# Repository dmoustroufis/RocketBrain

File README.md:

# RocketBrain
A flight computer for model rockets in a HAT format for the Raspberry Pi Pico

Hardware characteristics  : 
* Primary 9 axis IMU 
* Secondary 6 axis IMU 
* Barometer 
* 128kB flash chip for vibration-safe data logging  
* micro sd card slot for data logging 
* LoRa tranceiver with 10km range 
* Output for 2 servos for Thrust Vector Control 
* Output for a Reaction Wheel motor (external driver is needed for the motor)
* 2 pyro channels 

The brain of the device is the Raspberry Pi Pico,
an ultra affordable, dual core, 32-bit microcontroller running at 125MHz.

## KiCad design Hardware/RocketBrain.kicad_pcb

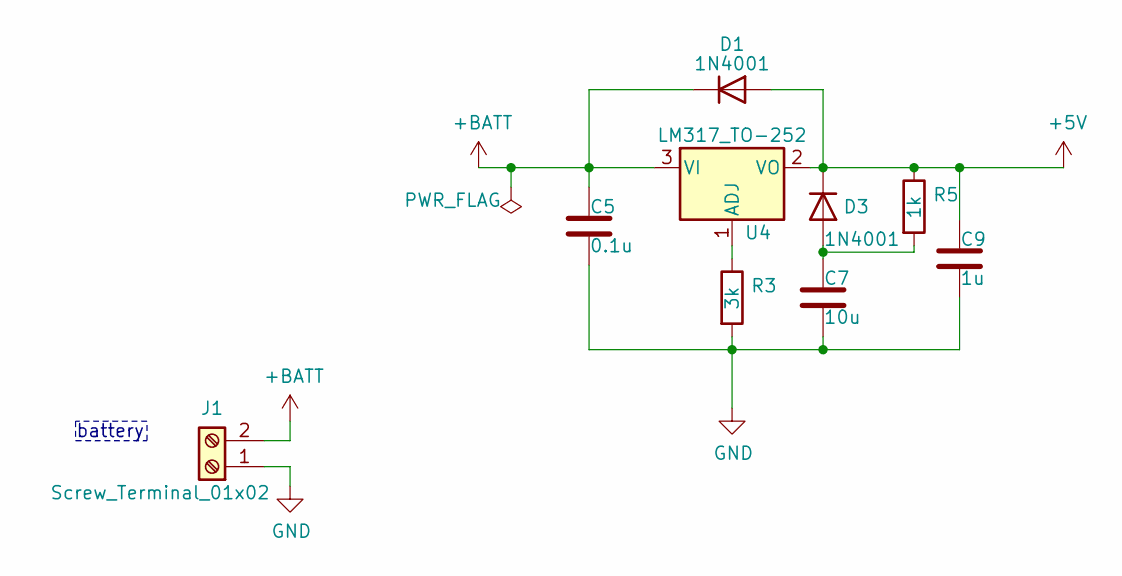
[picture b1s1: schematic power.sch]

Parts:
C5: 0.1u; C_0603_1608Metric
C7: 10u; C_0603_1608Metric
C9: 1u; C_0603_1608Metric
D1, D3: 1N4001; D_SOD-123F; Manufacturer_Part_Number 1N4001W
J1: Screw_Terminal_01x02; TerminalBlock_TE_282834-2_1x02_P2.54mm_Horizontal
R3: 3k; R_0603_1608Metric
R5: 1k; R_0603_1608Metric
U4: LM317_TO-252; TO-252-2; Manufacturer_Part_Number LM317AG-TN3-R

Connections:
+5V: C9.1, D1.2 (A), D3.1 (K), R5.1, U4.2 (VO); also elsewhere on the board
+BATT: C5.1, D1.1 (K), J1.2, U4.3 (VI); also elsewhere on the board
GND: C5.2, C7.2, C9.2, J1.1, R3.2; also elsewhere on the board
unnamed: C7.1, D3.2 (A), R5.2
unnamed: R3.1, U4.1 (ADJ)

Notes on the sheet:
battery

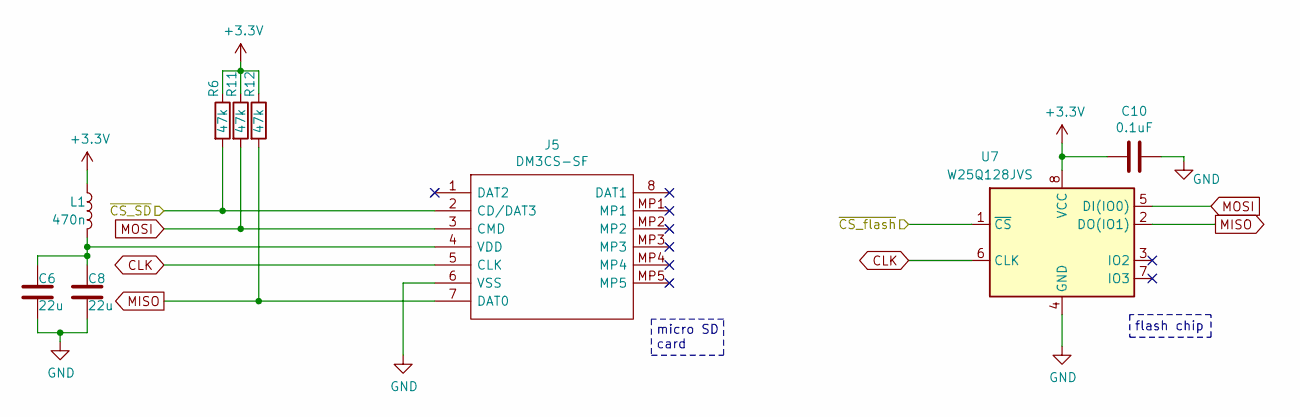
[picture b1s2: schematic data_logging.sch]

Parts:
C6, C8: 22u; C_0603_1608Metric
C10: 0.1uF; C_0603_1608Metric
J5: DM3CS-SF; DM3CSSF; Manufacturer_Part_Number DM3CS-SF; Mouser Part Number 798-DM3CSSF
L1: 470n; L_0603_1608Metric
R6, R11, R12: 47k; R_0603_1608Metric
U7: W25Q128JVS; SOIC-8_5.23x5.23mm_P1.27mm; Manufacturer_Part_Number W25Q128JVSIQ

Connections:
+3V3: C10.2, L1.1, R6.1, R11.1, R12.1, U7.8 (VCC); also elsewhere on the board
/Data Logging/~CS_SD: J5.2 (CD/DAT3), R6.2; also elsewhere on the board
/Data Logging/~CS_flash: U7.1 (~CS); also elsewhere on the board
CLK: J5.5 (CLK), U7.6 (CLK); also elsewhere on the board
GND: C6.2, C8.2, C10.1, J5.6 (VSS), U7.4 (GND); also elsewhere on the board
MISO: J5.7 (DAT0), R12.2, U7.2 (DO(IO1)); also elsewhere on the board
MOSI: J5.3 (CMD), R11.2, U7.5 (DI(IO0)); also elsewhere on the board
unnamed: C6.1, C8.1, J5.4 (VDD), L1.2

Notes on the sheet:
flash chip
micro SD card

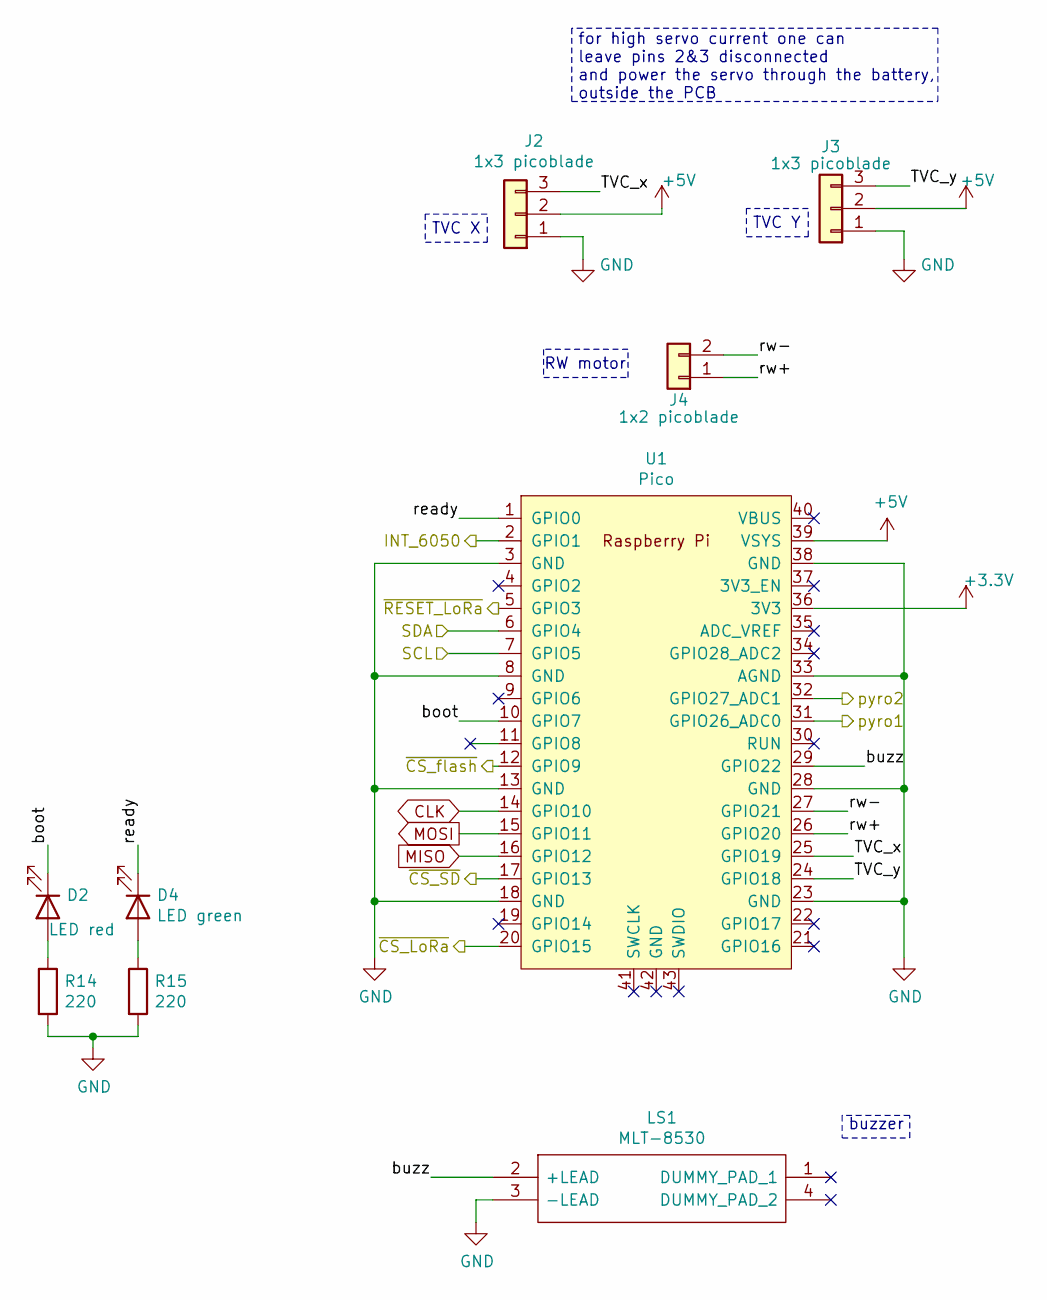
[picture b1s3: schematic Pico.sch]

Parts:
D2: LED red; LED_0603_1608Metric
D4: LED green; LED_0603_1608Metric
J2, J3: 1x3 picoblade; Molex_PicoBlade_53398-0371_1x03-1MP_P1.25mm_Vertical
J4: 1x2 picoblade; Molex_PicoBlade_53398-0271_1x02-1MP_P1.25mm_Vertical
LS1: MLT-8530; MLT8530; Manufacturer_Part_Number MLT-8530
R14, R15: 220; R_0603_1608Metric
U1: Pico; RPi_Pico_HAT_smd_mod

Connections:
+3V3: U1.36 (3V3); also elsewhere on the board
+5V: J2.2, J3.2, U1.39 (VSYS); also elsewhere on the board
/Data Logging/~CS_SD: U1.17 (GPIO13); also elsewhere on the board
/Data Logging/~CS_flash: U1.12 (GPIO9); also elsewhere on the board
/Pyro/pyro1: U1.31 (GPIO26_ADC0); also elsewhere on the board
/Pyro/pyro2: U1.32 (GPIO27_ADC1); also elsewhere on the board
/RPi Pico & Motors/INT_6050: U1.2 (GPIO1); also elsewhere on the board
/RPi Pico & Motors/SCL: U1.7 (GPIO5); also elsewhere on the board
/RPi Pico & Motors/SDA: U1.6 (GPIO4); also elsewhere on the board
/RPi Pico & Motors/TVC_x: J2.3, U1.25 (GPIO19)
/RPi Pico & Motors/TVC_y: J3.3, U1.24 (GPIO18)
/RPi Pico & Motors/boot: D2.1 (K), U1.10 (GPIO7)
/RPi Pico & Motors/buzz: LS1.2 (+LEAD), U1.29 (GPIO22)
/RPi Pico & Motors/ready: D4.1 (K), U1.1 (GPIO0)
/RPi Pico & Motors/rw+: J4.1, U1.26 (GPIO20)
/RPi Pico & Motors/rw-: J4.2, U1.27 (GPIO21)
/RPi Pico & Motors/~CS_LoRa: U1.20 (GPIO15); also elsewhere on the board
/RPi Pico & Motors/~RESET_LoRa: U1.5 (GPIO3); also elsewhere on the board
CLK: U1.14 (GPIO10); also elsewhere on the board
GND: J2.1, J3.1, LS1.3 (-LEAD), R14.2, R15.2, U1.3 (GND), U1.8 (GND), U1.13 (GND), U1.18 (GND), U1.23 (GND), U1.28 (GND), U1.33 (AGND), U1.38 (GND); also elsewhere on the board
MISO: U1.16 (GPIO12); also elsewhere on the board
MOSI: U1.15 (GPIO11); also elsewhere on the board
unnamed: D2.2 (A), R14.1
unnamed: D4.2 (A), R15.1

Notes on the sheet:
RW motor
TVC X
TVC Y
buzzer
for high servo current one can leave pins 2&3 disconnected and power the servo through the battery, outside the PCB

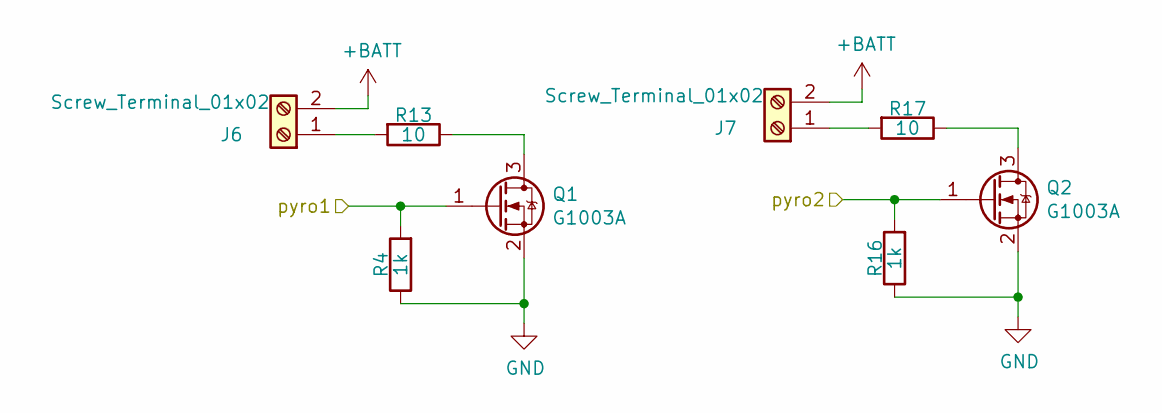
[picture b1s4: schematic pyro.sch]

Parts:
J6, J7: Screw_Terminal_01x02; TerminalBlock_TE_282834-2_1x02_P2.54mm_Horizontal
Q1, Q2: G1003A; SOT-23; Manufacturer_Part_Number G1003A
R4, R16: 1k; R_0603_1608Metric
R13, R17: 10; R_0603_1608Metric

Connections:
+BATT: J6.2, J7.2; also elsewhere on the board
/Pyro/pyro1: Q1.1 (G), R4.2; also elsewhere on the board
/Pyro/pyro2: Q2.1 (G), R16.2; also elsewhere on the board
GND: Q1.2 (S), Q2.2 (S), R4.1, R16.1; also elsewhere on the board
unnamed: J6.1, R13.2
unnamed: J7.1, R17.2
unnamed: Q1.3 (D), R13.1
unnamed: Q2.3 (D), R17.1

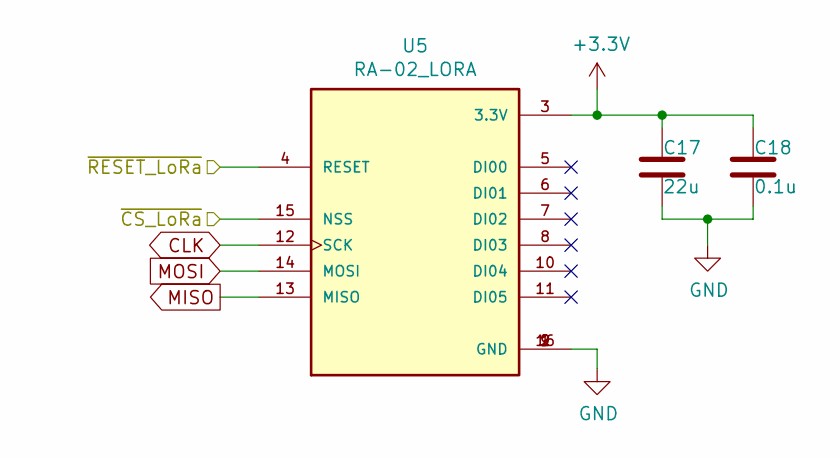
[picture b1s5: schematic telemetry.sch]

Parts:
C17: 22u; C_0603_1608Metric
C18: 0.1u; C_0603_1608Metric
U5: RA-02_LORA; MODULE_RA-02_LORA; PARTREV 2018/03/02

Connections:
+3V3: C17.1, C18.1, U5.3 (3.3V); also elsewhere on the board
/RPi Pico & Motors/~CS_LoRa: U5.15 (NSS); also elsewhere on the board
/RPi Pico & Motors/~RESET_LoRa: U5.4 (RESET); also elsewhere on the board
CLK: U5.12 (SCK); also elsewhere on the board
GND: C17.2, C18.2, U5.1 (GND), U5.2 (GND), U5.9 (GND), U5.16 (GND); also elsewhere on the board
MISO: U5.13 (MISO); also elsewhere on the board
MOSI: U5.14 (MOSI); also elsewhere on the board

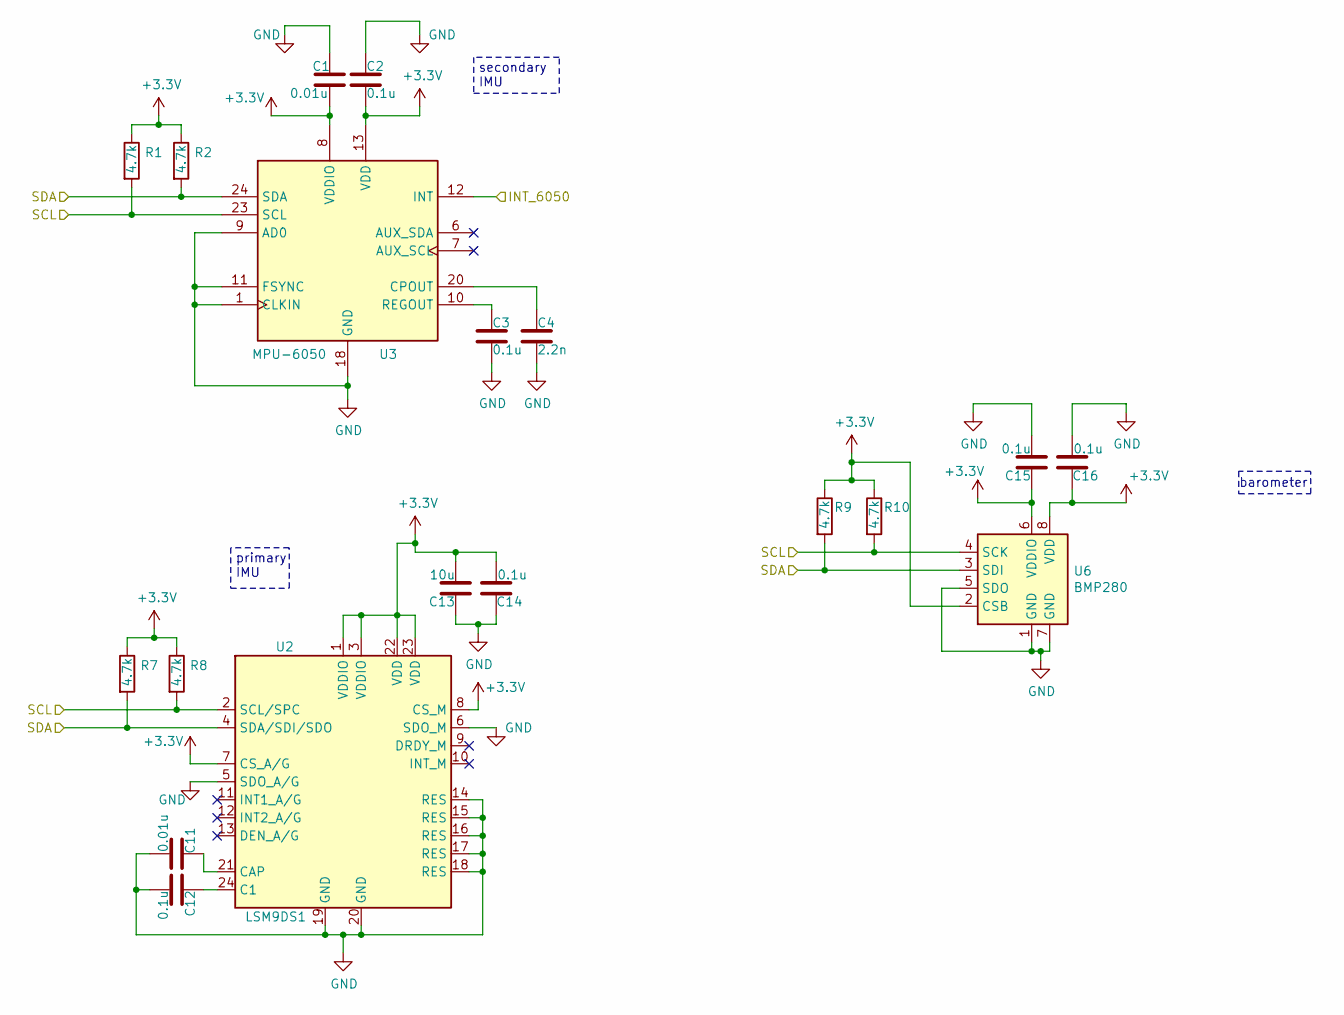
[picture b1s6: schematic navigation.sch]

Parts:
C1, C11: 0.01u; C_0603_1608Metric
C2, C3, C12, C14, C15, C16: 0.1u; C_0603_1608Metric
C4: 2.2n; C_0603_1608Metric
C13: 10u; C_0603_1608Metric
R1, R2, R7, R8, R9, R10: 4.7k; R_0603_1608Metric
U2: LSM9DS1; LGA-24L_3x3.5mm_P0.43mm; Manufacturer_Part_Number LSM9DS1
U3: MPU-6050; InvenSense_QFN-24_4x4mm_P0.5mm; Manufacturer_Part_Number MPU-6050
U6: BMP280; Bosch_LGA-8_2x2.5mm_P0.65mm_ClockwisePinNumbering; Manufacturer_Part_Number BMP280

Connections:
+3V3: C1.2, C2.2, C13.2, C14.2, C15.1, C16.1, R1.1, R2.1, R7.1, R8.1, R9.1, R10.1, U2.1 (VDDIO), U2.3 (VDDIO), U2.7 (CS_A/G), U2.8 (CS_M), U2.22 (VDD), U2.23 (VDD), U3.8 (VDDIO), U3.13 (VDD), U6.2 (CSB), U6.6 (VDDIO), U6.8 (VDD); also elsewhere on the board
/RPi Pico & Motors/INT_6050: U3.12 (INT); also elsewhere on the board
/RPi Pico & Motors/SCL: R1.2, R8.2, R10.2, U2.2 (SCL/SPC), U3.23 (SCL), U6.4 (SCK); also elsewhere on the board
/RPi Pico & Motors/SDA: R2.2, R7.2, R9.2, U2.4 (SDA/SDI/SDO), U3.24 (SDA), U6.3 (SDI); also elsewhere on the board
GND: C1.1, C2.1, C3.2, C4.2, C11.2, C12.2, C13.1, C14.1, C15.2, C16.2, U2.5 (SDO_A/G), U2.6 (SDO_M), U2.14 (RES), U2.15 (RES), U2.16 (RES), U2.17 (RES), U2.18 (RES), U2.19 (GND), U2.20 (GND), U3.1 (CLKIN), U3.9 (AD0), U3.11 (FSYNC), U3.18 (GND), U6.1 (GND), U6.5 (SDO), U6.7 (GND); also elsewhere on the board
unnamed: C3.1, U3.10 (REGOUT)
unnamed: C4.1, U3.20 (CPOUT)
unnamed: C11.1, U2.21 (CAP)
unnamed: C12.1, U2.24 (C1)

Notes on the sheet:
secondary IMU
primary IMU
barometer

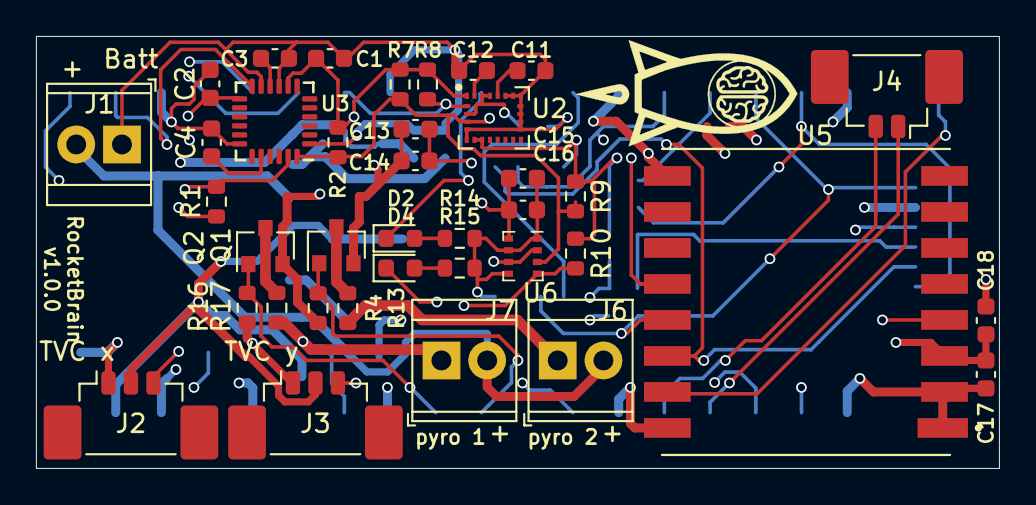
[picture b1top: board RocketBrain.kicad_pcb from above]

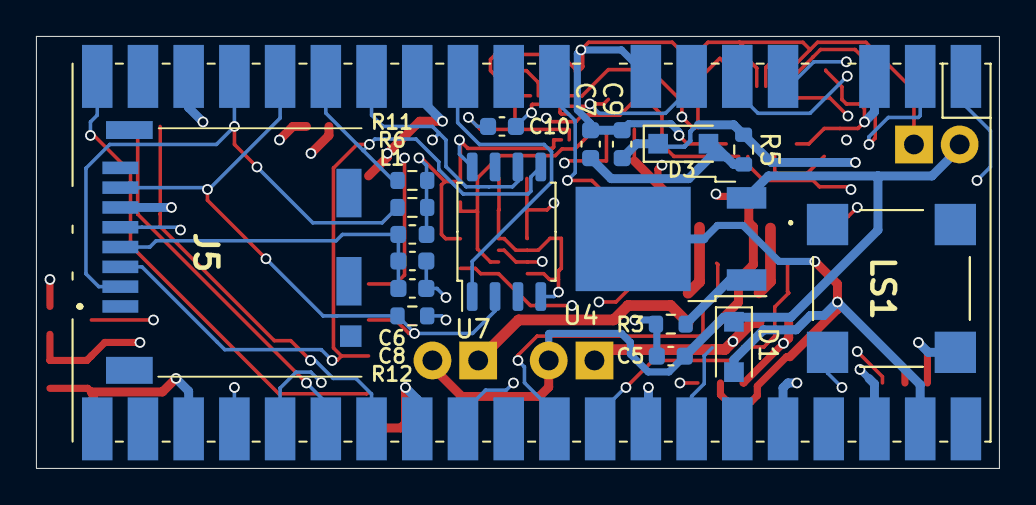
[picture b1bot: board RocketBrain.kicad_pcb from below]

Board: 4 copper layers, 53.5 x 24.0 mm, 57 parts (19 on the bottom side), 36 nets.

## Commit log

2021-08-09 Create gitignore
2021-08-09 Inital HW commit
2021-08-11 Add 2nd pyro, smd headers
2021-08-15 Update schematic, component placement
2021-08-15 Update component placement
2021-08-20 Update schematic and routing
2021-08-23 Modify RPi Pico footprint, update routing
2021-08-23 Update silkscreen
2021-08-23 Widen board, reposition LoRa capacitors
2021-08-24 Create LICENSE
2021-08-24 Change regulator diode footprint, update routing
